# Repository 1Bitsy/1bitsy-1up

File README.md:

This repository contains the board and code used on the 1Bitsy 1UP.

## Intro

1Bitsy 1UP is a retro inspired handheld game console, the design is based
around the following __semi arbitrary constraints and requirements.__

* Formfactor: PCB the size of the inside of a GB DMG (the gray one) This will
  hopefully eventually allow us to put the 1UP pcb inside a modified GB DMG
  case, either original or new molds sold by several online stores.
* Main CPU: All code should be able to execute on a 1Bitsy that is fitted with
  an STM32F415RGT6. That particular chip (due to the package size) does not
  contain external ram support or LCD display engine. Making LCD drive little
  bit more tricky. It is a nice constraint that makes coding for the platform
  bit more of a challenge in the style of classic conloles and 8bit computers
  because it does not have enough memory for a full framebuffer. ("racing the
  beam" FTW)
* Main CPU Mounting: The board contains the 1Bitsy compatible low profile
  socket using [SL-115-TT-19](https://www.samtec.com/products/sl-115-tt-19)
  and [BBL-115-T-E](https://www.samtec.com/products/bbl-115-t-e) Samtec
  connectors as well as one MillMax PogoPin spring loaded SMD connector.
* LCD: The LCD is a 240x320 TFT display with capacitive touch, connected
  through the 8bit parallel interface to the 1Bitsy. This allows us to push the
  data speed to the display quite high and reach good framerates that would not
  be possible through the SPI interface. The capacitive touch screen adds an
  interesting aspect of control that was not available on classic consoles
  prior to DS. (That was also resistive not capacitive)
* Audio: We are connecting the STM32F4 built in DAC lines for audio generation.
  This is not as slick and good as an i2s part but will likely make things
  "interesting".
* Controls: The gamepad consists of the classic D-Pad, ABXY, Select, Start set
  of buttons. Because we have the capacitive touch no other analog controls are
  considered necessary.
* Storage: To simplify storing games and data in large quantities we have
  connected a microSD card over the SDIO interface to the STM32, allowing for
  reasonabely fast load and save times and maybe even some other interesting
  hacks.
* Expansion: The platform will receive future expansions and improvements that
  will strive to remain transparent. Meaning all code written for the first
  version of the platform should work either out of the box or only with very
  minor modifications.

The display used is a TFT LCD with I2C CapTouch and ILI9341 driver.

__The most basic design consists of:__
* 1Bitsy STM32F415RGT6 (168MHz, 192kb RAM, 1MB Flash)
* 240x320 2.8" TFT with capacitive touch and PWM backlight control
* D-Pad, ABXY, Start, Select buttons
* DAC audio out to headphones. (speakers optional)
* SDCard connected over SDIO interface

Second tier addons for quality of life:
* Lipo battery and charger built in
* Speaker audio

__Future "transparent" expansions:__
These expansions will contribute to new and interesting hacks possible on the
platform, they are not considered forward compatible but backward compatible.
This means that we do not anticipate the expansions to exist from the beginning
of the platform life and the software written at that time will not support the
future expansions, but the old software has to function as is or only with very
minor changes on the new device that contains the new expansions.

## Hacking

The board design is in the hardware subdirectory.

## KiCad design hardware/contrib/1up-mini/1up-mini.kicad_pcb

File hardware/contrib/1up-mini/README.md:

# 1up-mini

This is a board based on 1up v0.2, with horizontal form factor and easier to
solder by hand.

It is not supported by 1bit squared.

## What changed?

It aims to be fully compatible with 1up board. Some of the components are
changed to avoid hard to solder packages:

- Headphone amplifier reference is changed. It consumes more power than the
  one used on the original board.
- Volume control is the same component, with a different package.
- Battery charger and power path is split in two components.
- 0402 footprints are replaced with 0603.
- Touch screen signals are only connected to 6 pin connector.

Board shape is horizontal with symmetric buttons on both sides.

## What to change for the next iteration?

- 0603 and resistor network footprints are a little bit to small for hand
  soldering.
- SD card slot must be changed for something easier to solder.
- Headphone jack could be changed for something more solid.
- Hole for pogo pin is too small. Add a large pad so that it can be replaced
  with a cable.
- Switch are hard to source. Also the one I ordered are not so good.

## Assembly

Some tricky points:

- You will need solder paste, flux and hot air to solder the SD card slot.
- Surface under the LCD should be flat. Cut the pin used to mount the 1bitsy
  before soldering. Use isolating tape to avoid short circuits (there is a
  metal shield under the LCD).
- You can replace the pogo pin with a cable.

## BOM

| Reference              | Package    | Qty. | Designation     | Mouser/URL           |
| ---------------------- | ---------- | ---- | --------------- | -------------------- |
| C[19,26,27,29,30]      | 0603       | 5    | 100 nF          |                      |
| C[20,21,24,25,31..33]  | 0603       | 7    | 1 µF            |                      |
| C[22,23]               | 0603       | 2    | 2.2 µF          |                      |
| C28                    | 0805       | 1    | 10 µF           |                      |
| CON1                   | SCHA4B0419 | 1    | Micro SD        | 688-SCHA4B0419       |
| D2                     | 0603       | 1    | Yellow LED      |                      |
| J3                     | Jack       | 1    | JACK_3C1S       | 490-SJ2-35853BSMT-TR |
| P1                     | PogoPin    | 1    | PogoPin         | 575-906115 or cable  |
| P[2..4]                |            | 3    | Battery conn.   |                      |
| Q1                     | SOT-23     | 1    | NMOS            | 726-BSS806NH6327XT   |
| R11                    | 0603       | 1    | 49 kΩ           |                      |
| R[12..15]              | 4x0603     | 4    | 10 kΩ           | 667-EXB-38V103JV     |
| R[17,18]               | 0603       | 2    | 2.7 kΩ          |                      |
| R[20..23]              | 0603       | 4    | 10 Ω            |                      |
| R24                    | 0603       | 1    | 1 kΩ            |                      |
| R6                     | 0603       | 1    | 4.7 kΩ          |                      |
| R[7,10,16,19,25,26,30] | 0603       | 7    | 10 kΩ           |                      |
| R[8,9]                 | 0603       | 2    | 50 Ω            |                      |
| SW[12,13]              | Switch     | 2    | Side Switch     | 653-B3U-3000P        |
| SW14                   | Switch     | 1    | SPDT Switch     | 611-PCM12SMTR        |
| SW[2..11]              | Switch     | 1    | Switch          | [aliexpress][]       |
| U10                    | TSSOP-8    | 1    | TPS2111A        | 595-TPS2111APWR      |
| U2                     | 1bitsy     | 1    | 1bitsy          |                      |
| U3                     | TSSOP-14   | 1    | MCP4661-103E/ST | 579-MCP4661-103E/ST  |
| U4                     | TSSOP-14   | 1    | TPA6139A2-PW    | 595-TPA6139A2PWR     |
| U[5,6]                 | TSSOP-16   | 2    | 74HC165         | 771-74HC165PW-T      |
| U7                     | SOT-23-6   | 1    | BQ21040         | 595-BQ21040DBVR      |
| U8                     | ER-CON50HT | 1    | 50 pin conn.    | sold with LCD        |
| U9                     | ER-CON06HB | 1    | 6 pin conn.     | sold with LCD        |
| LCD                    |            | 1    | LCD             | [buydisplay][]       |

[buydisplay]:
  http://www.buydisplay.com/default/serial-spi-2-8-tft-lcd-module-display-320x240-optional-touch-screen
[aliexpress]:
  https://www.aliexpress.com/store/product/Original-new-100-Japan-conductive-rubber-head-waterproof-touch-switch-8-8-5-silent-key-micro/828867_32724415032.html

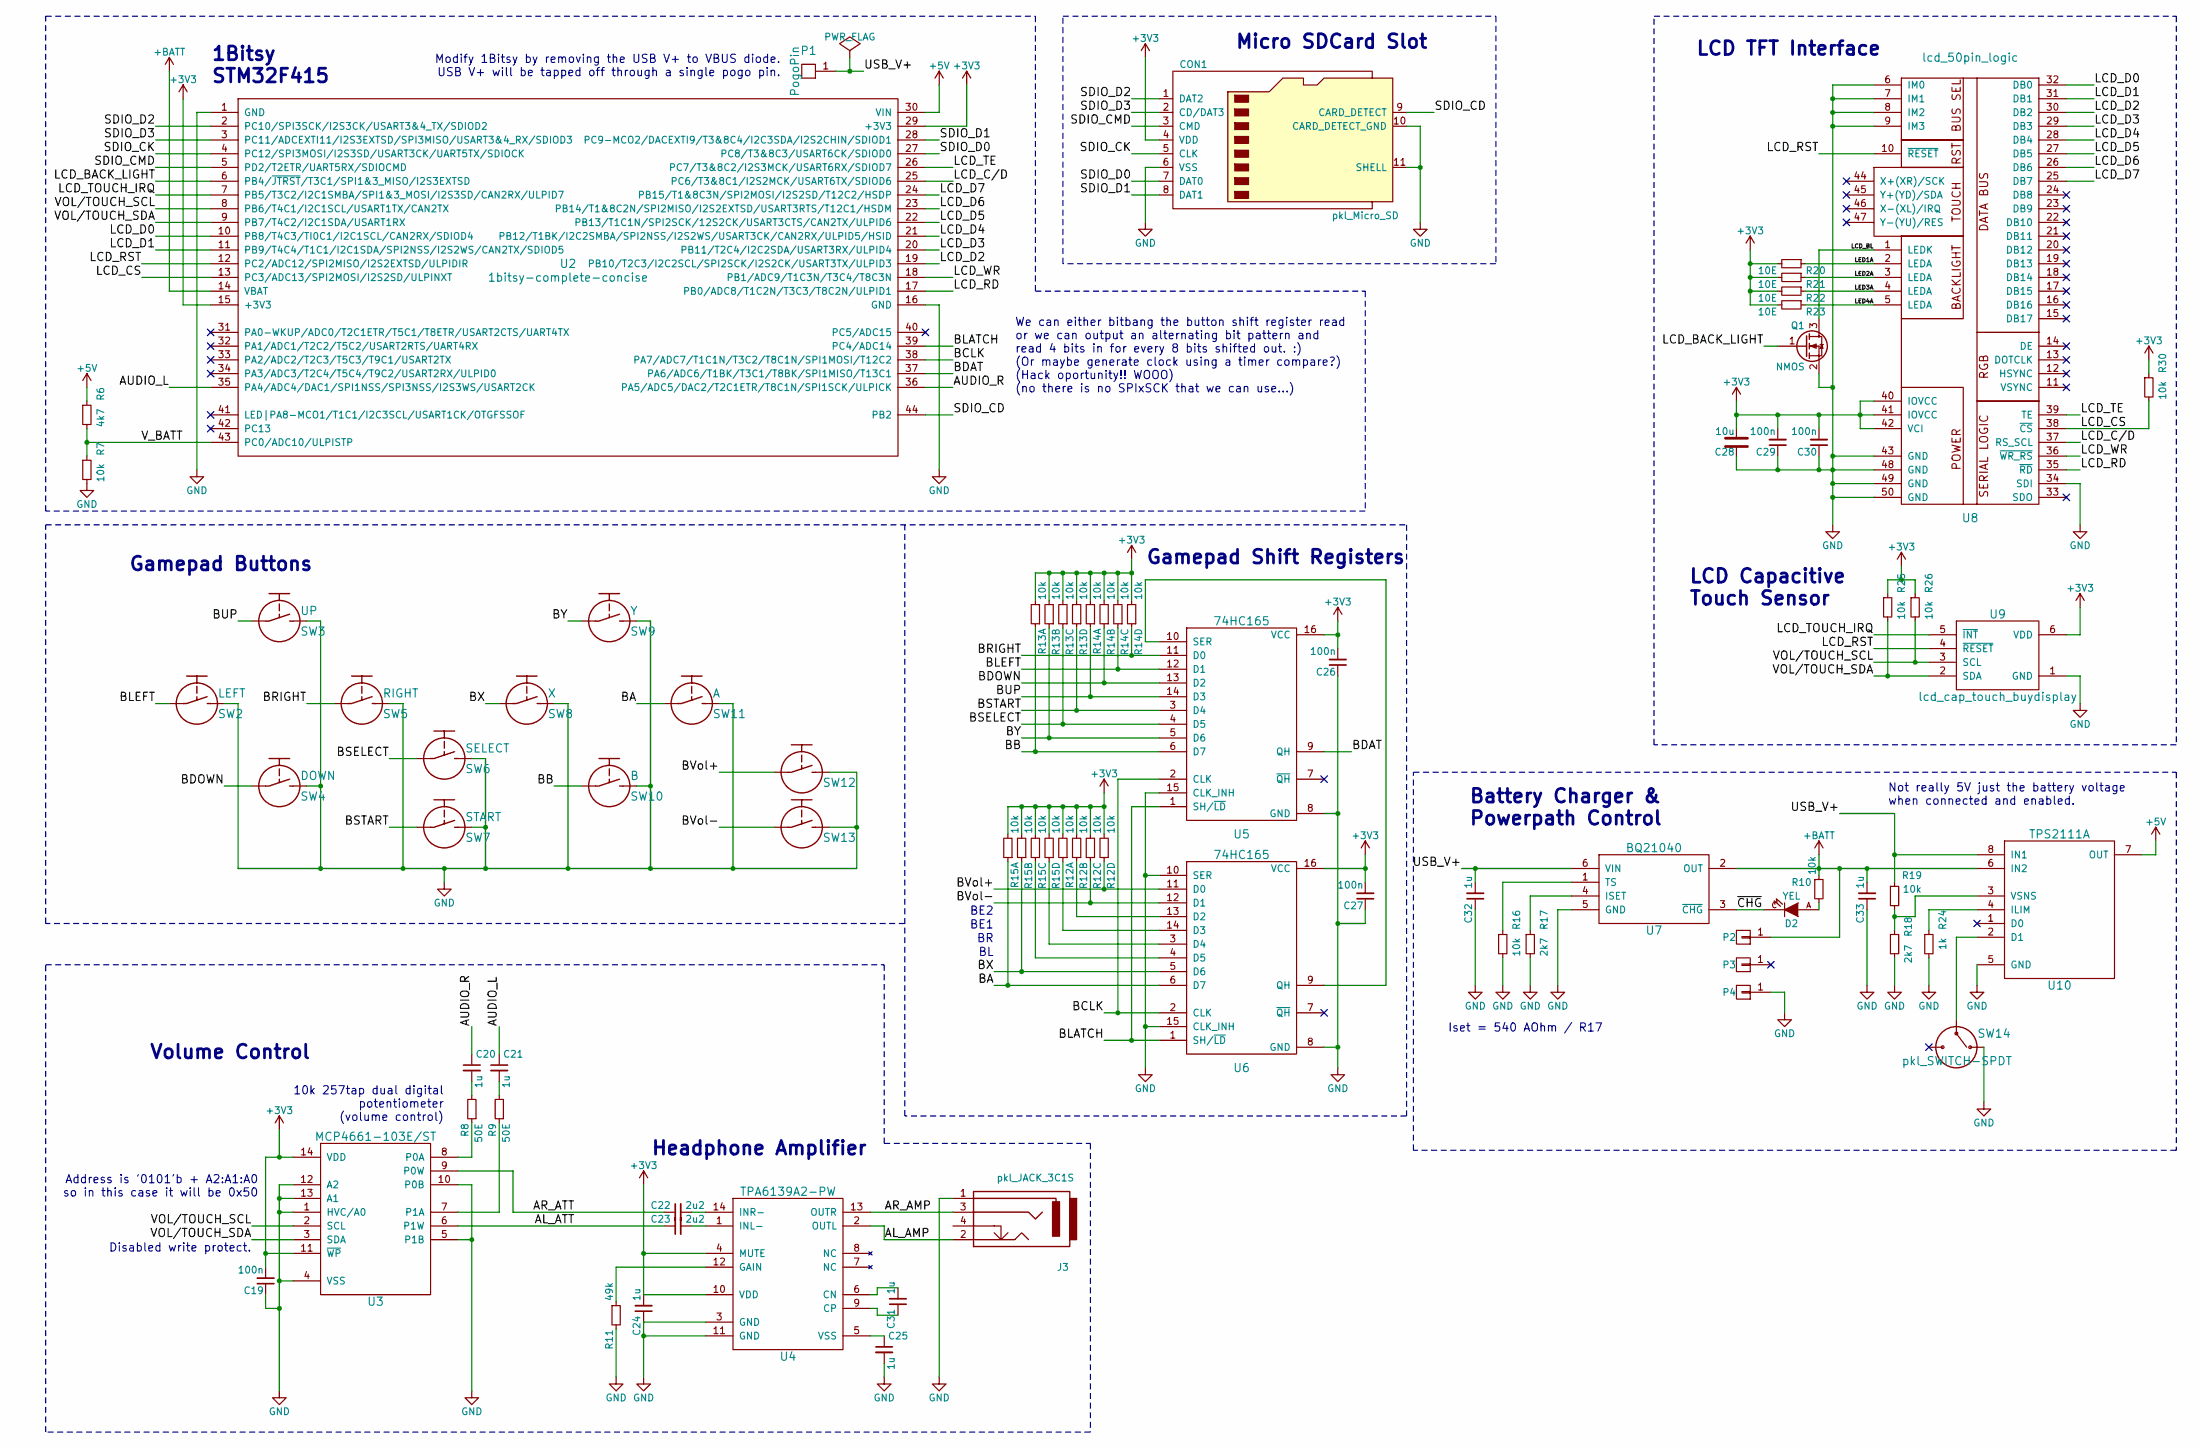
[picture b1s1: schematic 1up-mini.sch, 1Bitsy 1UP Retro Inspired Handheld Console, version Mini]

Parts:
C19, C26, C27, C29, C30: 100n; C_0603
C20, C21, C24, C25, C31, C32, C33: 1u; C_0603
C22, C23: 2u2; C_0603
C28: 10u; C_0805
CON1: pkl_Micro_SD; SCHA4B0419
D2: YEL; D_0603
J3: pkl_JACK_3C1S; SJ2-35853B-SMT
P1: PogoPin; PAD_MILL-MAX_0906
P2, P3, P4: CONN_01X01; Pin_Header_Straight_Round_1x01
Q1: NMOS; SOT-23
R6: 4k7; R_0603
R7, R10, R16, R19, R25, R26, R30: 10k; R_0603
R8, R9: 50E; R_0603
R11: 49k; R_0603
R12, R13, R14, R15: 10k; R_Array_Concave_4x0603
R17, R18: 2k7; R_0603
R20, R21, R22, R23: 10E; R_0603
R24: 1k; R_0603
SW2: LEFT; Tact_Switch_Top_TH_7.8MM_Snap
SW3: UP; Tact_Switch_Top_TH_7.8MM_Snap
SW4: DOWN; Tact_Switch_Top_TH_7.8MM_Snap
SW5: RIGHT; Tact_Switch_Top_TH_7.8MM_Snap
SW6: SELECT; Tact_Switch_Top_TH_7.8MM_Snap
SW7: START; Tact_Switch_Top_TH_7.8MM_Snap
SW8: X; Tact_Switch_Top_TH_7.8MM_Snap
SW9: Y; Tact_Switch_Top_TH_7.8MM_Snap
SW10: B; Tact_Switch_Top_TH_7.8MM_Snap
SW11: A; Tact_Switch_Top_TH_7.8MM_Snap
SW12, SW13: Tact_Switch_Side_B3U-3000P
SW14: pkl_SWITCH-SPDT; SW_SPDT_PCM12
U2: 1bitsy-complete-concise; 1bitsy-sl-1xx-xx-19
U3: MCP4661-103E/ST; TSSOP-14_4.4x5mm_Pitch0.65mm
U4: TPA6139A2-PW; TSSOP-14_4.4x5mm_Pitch0.65mm
U5, U6: 74HC165; TSSOP-16_4.4x5mm_Pitch0.65mm
U7: BQ21040; SOT-23-6
U8: lcd_50pin_logic; ER-CON50HT
U9: lcd_cap_touch_buydisplay; ER-CON06HB
U10: TPS2111A; TSSOP-8_4.4x3mm_Pitch0.65mm

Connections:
+3V3: C19.2, C24.2, C26.2, C27.2, C28.2, C29.2, C30.2, CON1.4 (VDD), R12.2, R12.4, R12.6, R12.8, R13.2, R13.4, R13.6, R13.8, R14.2, R14.4, R14.6, R14.8, R15.2, R15.4, R15.6, R15.8, R20.2, R21.2, R22.2, R23.2, R25.1, R26.1, R30.1, U2.15 (+3V3), U2.29 (+3V3), U3.11 (~WP), U3.14 (VDD), U4.4 (MUTE), U4.10 (VDD), U5.16 (VCC), U6.16 (VCC), U8.40 (IOVCC), U8.41 (IOVCC), U8.42 (VCI), U9.6 (VDD)
+5V: R6.1, U2.30 (VIN), U10.7 (OUT)
+BATT: C33.2, P2.1, R10.1, U2.14 (VBAT), U7.2 (OUT), U10.6 (IN2)
/AL_AMP: J3.2, U4.2 (OUTL)
/AL_ATT: C23.1, U3.6 (P1W)
/AR_AMP: J3.3, U4.13 (OUTR)
/AR_ATT: C22.1, U3.9 (P0W)
/AUDIO_L: C21.1, U2.35 (PA4/ADC4/DAC1/SPI1NSS/SPI3NSS/I2S3WS/US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)
/AUDIO_R: C20.1, U2.36 (PA5/ADC5/DAC2/T2C1ETR/T8C1N/SPI1SCK/ULP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)
/BA: R15.1, SW11.1, U6.6 (D7)
/BB: R13.1, SW10.1, U5.6 (D7)
/BCLK: U2.38 (PA7/ADC7/T1C1N/T3C2/T8C1N/SPI1MOSI/T12C2), U5.2 (CLK), U6.2 (CLK)
/BDAT: U2.37 (PA6/ADC6/T1BK/T3C1/T8BK/SPI1MISO/T13C1), U5.9 (QH)
/BDOWN: R14.3, SW4.1, U5.13 (D2)
/BLATCH: U2.39 (PC4/ADC14), U5.1 (SH/~LD), U6.1 (SH/~LD)
/BLEFT: R14.5, SW2.1, U5.12 (D1)
/BRIGHT: R14.7, SW5.1, U5.11 (D0)
/BSELECT: R13.5, SW6.1, U5.4 (D5)
/BSTART: R13.7, SW7.1, U5.3 (D4)
/BUP: R14.1, SW3.1, U5.14 (D3)
/BVol+: R12.7, SW12.1, U6.11 (D0)
/BVol-: R12.5, SW13.1, U6.12 (D1)
/BX: R15.3, SW8.1, U6.5 (D6)
/BY: R13.3, SW9.1, U5.5 (D6)
/LCD_BACK_LIGHT: Q1.1 (G), U2.6 (PB4/~JTRST~/T3C1/SPI1&3_MISO/I2S3EXTSD)
/LCD_BL: Q1.3 (D), U8.1 (LEDK)
/LCD_C/D: U2.25 (PC6/T3&8C1/I2S2MCK/USART6TX/SDIOD6), U8.37 (RS_SCL)
/LCD_CS: R30.2, U2.13 (PC3/ADC13/SPI2MOSI/I2S2SD/ULPINXT), U8.38 (~CS)
/LCD_D0: U2.10 (PB8/T4C3/TI0C1/I2C1SCL/CAN2RX/SDIOD4), U8.32 (DB0)
/LCD_D1: U2.11 (PB9/T4C4/T1C1/I2C1SDA/SPI2NSS/I2S2WS/CA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), U8.31 (DB1)
/LCD_D2: U2.19 (PB10/T2C3/I2C2SCL/SPI2SCK/I2S2CK/USART3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), U8.30 (DB2)
/LCD_D3: U2.20 (PB11/T2C4/I2C2SDA/USART3RX/ULPID4), U8.29 (DB3)
/LCD_D4: U2.21 (PB12/T1BK/I2C2SMBA/SPI2NSS/I2S2WS/USART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), U8.28 (DB4)
/LCD_D5: U2.22 (PB13/T1C1N/SPI2SCK/12S2CK/USART3CTS/CAN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), U8.27 (DB5)
/LCD_D6: U2.23 (PB14/T1&8C2N/SPI2MISO/I2S2EXTSD/USART3R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), U8.26 (DB6)
/LCD_D7: U2.24 (PB15/T1&8C3N/SPI2MOSI/I2S2SD/T12C2/HSDP), U8.25 (DB7)
/LCD_RD: U2.17 (PB0/ADC8/T1C2N/T3C3/T8C2N/ULPID1), U8.35 (~RD)
/LCD_RST: U2.12 (PC2/ADC12/SPI2MISO/I2S2EXTSD/ULPIDIR), U8.10 (~RESET), U9.4 (~RESET)
/LCD_TE: U2.26 (PC7/T3&8C2/I2S3MCK/USART6RX/SDIOD7), U8.39 (TE)
/LCD_TOUCH_IRQ: U2.7 (PB5/T3C2/I2C1SMBA/SPI1&3_MOSI/I2S3SD/CA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), U9.5 (~INT)
/LCD_WR: U2.18 (PB1/ADC9/T1C3N/T3C4/T8C3N), U8.36 (~WR_RS)
/LED1A: R20.1, U8.2 (LEDA)
/LED2A: R21.1, U8.3 (LEDA)
/LED3A: R22.1, U8.4 (LEDA)
/LED4A: R23.1, U8.5 (LEDA)
/SDIO_CD: CON1.9 (CARD_DETECT), U2.44 (PB2)
/SDIO_CK: CON1.5 (CLK), U2.4 (PC12/SPI3MOSI/I2S3SD/USART3CK/UART5TX/S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)
/SDIO_CMD: CON1.3 (CMD), U2.5 (PD2/T2ETR/UART5RX/SDIOCMD)
/SDIO_D0: CON1.7 (DAT0), U2.27 (PC8/T3&8C3/USART6CK/SDIOD0)
/SDIO_D1: CON1.8 (DAT1), U2.28 (PC9-MCO2/DACEXTI9/T3&8C4/I2C3SDA/I2S2CH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)
/SDIO_D2: CON1.1 (DAT2), U2.2 (PC10/SPI3SCK/I2S3CK/USART3&4_TX/SDIOD2)
/SDIO_D3: CON1.2 (CD/DAT3), U2.3 (PC11/ADCEXTI11/I2S3EXTSD/SPI3MISO/USART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)
/USB_V+: C32.2, P1.1, R19.1, U7.6 (VIN), U10.8 (IN1)
/VOL/TOUCH_SCL: R26.2, U2.8 (PB6/T4C1/I2C1SCL/USART1TX/CAN2TX), U3.2 (SCL), U9.3 (SCL)
/VOL/TOUCH_SDA: R25.2, U2.9 (PB7/T4C2/I2C1SDA/USART1RX), U3.3 (SDA), U9.2 (SDA)
/V_BATT: R6.2, R7.1, U2.43 (PC0/ADC10/ULPISTP)
/~CHG: D2.C, U7.3 (~CHG)
GND: C19.1, C24.1, C25.2, C26.1, C27.1, C28.1, C29.1, C30.1, C32.1, C33.1, CON1.6 (VSS), CON1.10 (CARD_DETECT_GND), CON1.11 (SHELL), J3.1, P4.1, Q1.2 (S), R7.2, R11.2, R16.2, R17.2, R18.2, R24.2, SW2.2, SW3.2, SW4.2, SW5.2, SW6.2, SW7.2, SW8.2, SW9.2, SW10.2, SW11.2, SW12.2, SW13.2, SW14.1, U2.1 (GND), U2.16 (GND), U3.1 (HVC/A0), U3.4 (VSS), U3.5 (P1B), U3.10 (P0B), U3.12 (A2), U3.13 (A1), U4.3 (GND), U4.11 (GND), U5.8 (GND), U5.15 (CLK_INH), U6.8 (GND), U6.10 (SER), U6.15 (CLK_INH), U7.5 (GND), U8.6 (IM0), U8.7 (IM1), U8.8 (IM2), U8.9 (IM3), U8.34 (SDI), U8.43 (GND), U8.48 (GND), U8.49 (GND), U8.50 (GND), U9.1 (GND), U10.5 (GND)
unnamed: C20.2, R8.2
unnamed: C21.2, R9.2
unnamed: C22.2, U4.14 (INR-)
unnamed: C23.2, U4.1 (INL-)
unnamed: C25.1, U4.5 (VSS)
unnamed: C31.1, U4.9 (CP)
unnamed: C31.2, U4.6 (CN)
unnamed: D2.A, R10.2
unnamed: R8.1, U3.8 (P0A)
unnamed: R9.1, U3.7 (P1A)
unnamed: R11.1, U4.12 (GAIN)
unnamed: R12.1, U6.14 (D3)
unnamed: R12.3, U6.13 (D2)
unnamed: R15.5, U6.4 (D5)
unnamed: R15.7, U6.3 (D4)
unnamed: R16.1, U7.1 (TS)
unnamed: R17.1, U7.4 (ISET)
unnamed: R18.1, R19.2, U10.3 (VSNS)
unnamed: R24.1, U10.4 (ILIM)
unnamed: SW14.2, U10.2 (D1)
unnamed: U5.10 (SER), U6.9 (QH)

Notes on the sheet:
BE1
BE2
Not really 5V just the battery voltage when connected and enabled.
Address is '0101'b + A2:A1:A0 so in this case it will be 0x50
Disabled write protect.
10k 257tap dual digital potentiometer (volume control)
LCD TFT Interface
LCD Capacitive Touch Sensor
Gamepad Buttons
Gamepad Shift Registers
Battery Charger & Powerpath Control
Volume Control
Headphone Amplifier
Iset = 540 AOhm / R17
Modify 1Bitsy by removing the USB V+ to VBUS diode. USB V+ will be tapped off through a single pogo pin.
We can either bitbang the button shift register read or we can output an alternating bit pattern and read 4 bits in for every 8 bits shifted out. :) (Or maybe generate clock using a timer compare?) (Hack oportunity!! WOOO) (no there is no SPIxSCK that we can use...)
Micro SDCard Slot
1Bitsy STM32F415

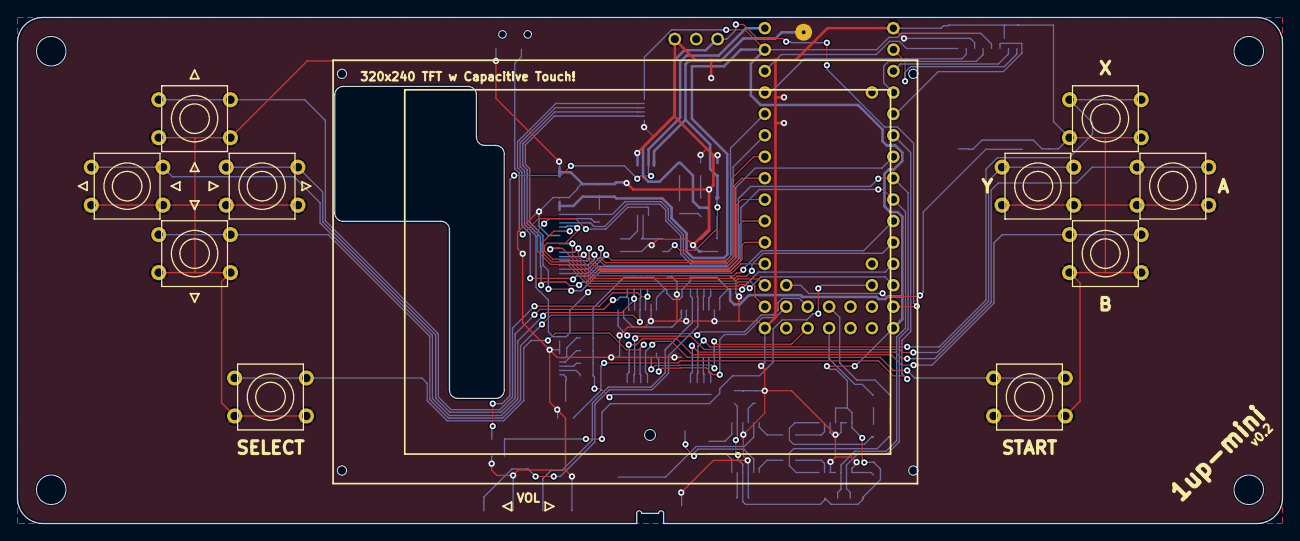
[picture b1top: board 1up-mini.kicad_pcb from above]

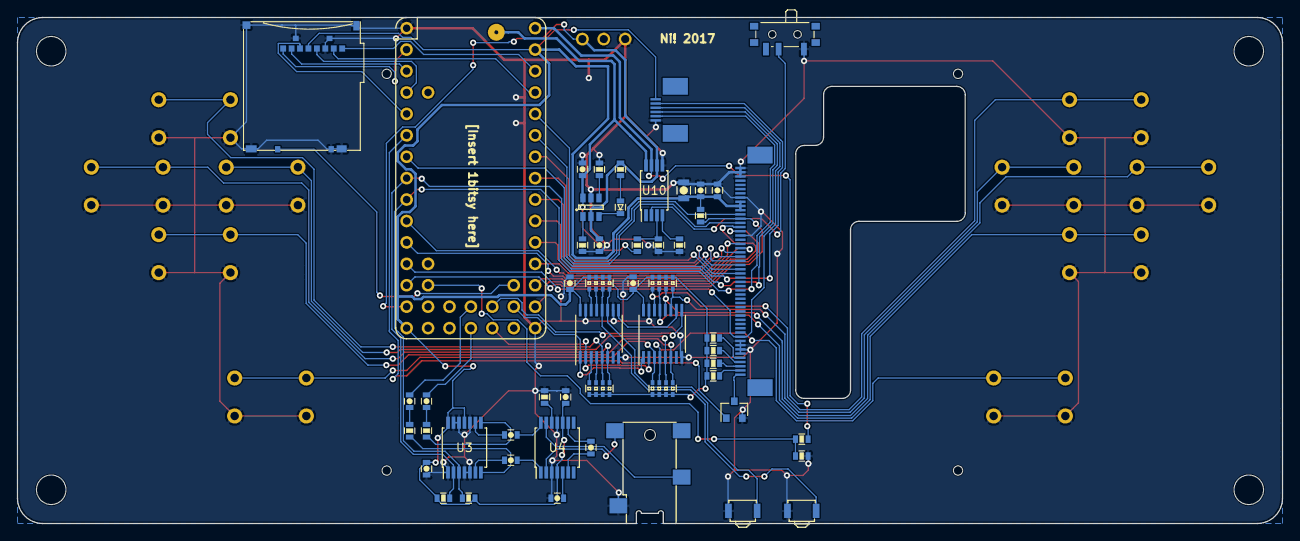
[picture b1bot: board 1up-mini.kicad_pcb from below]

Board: 2 copper layers, 150.0 x 60.0 mm, 67 parts (57 on the bottom side), 79 nets.

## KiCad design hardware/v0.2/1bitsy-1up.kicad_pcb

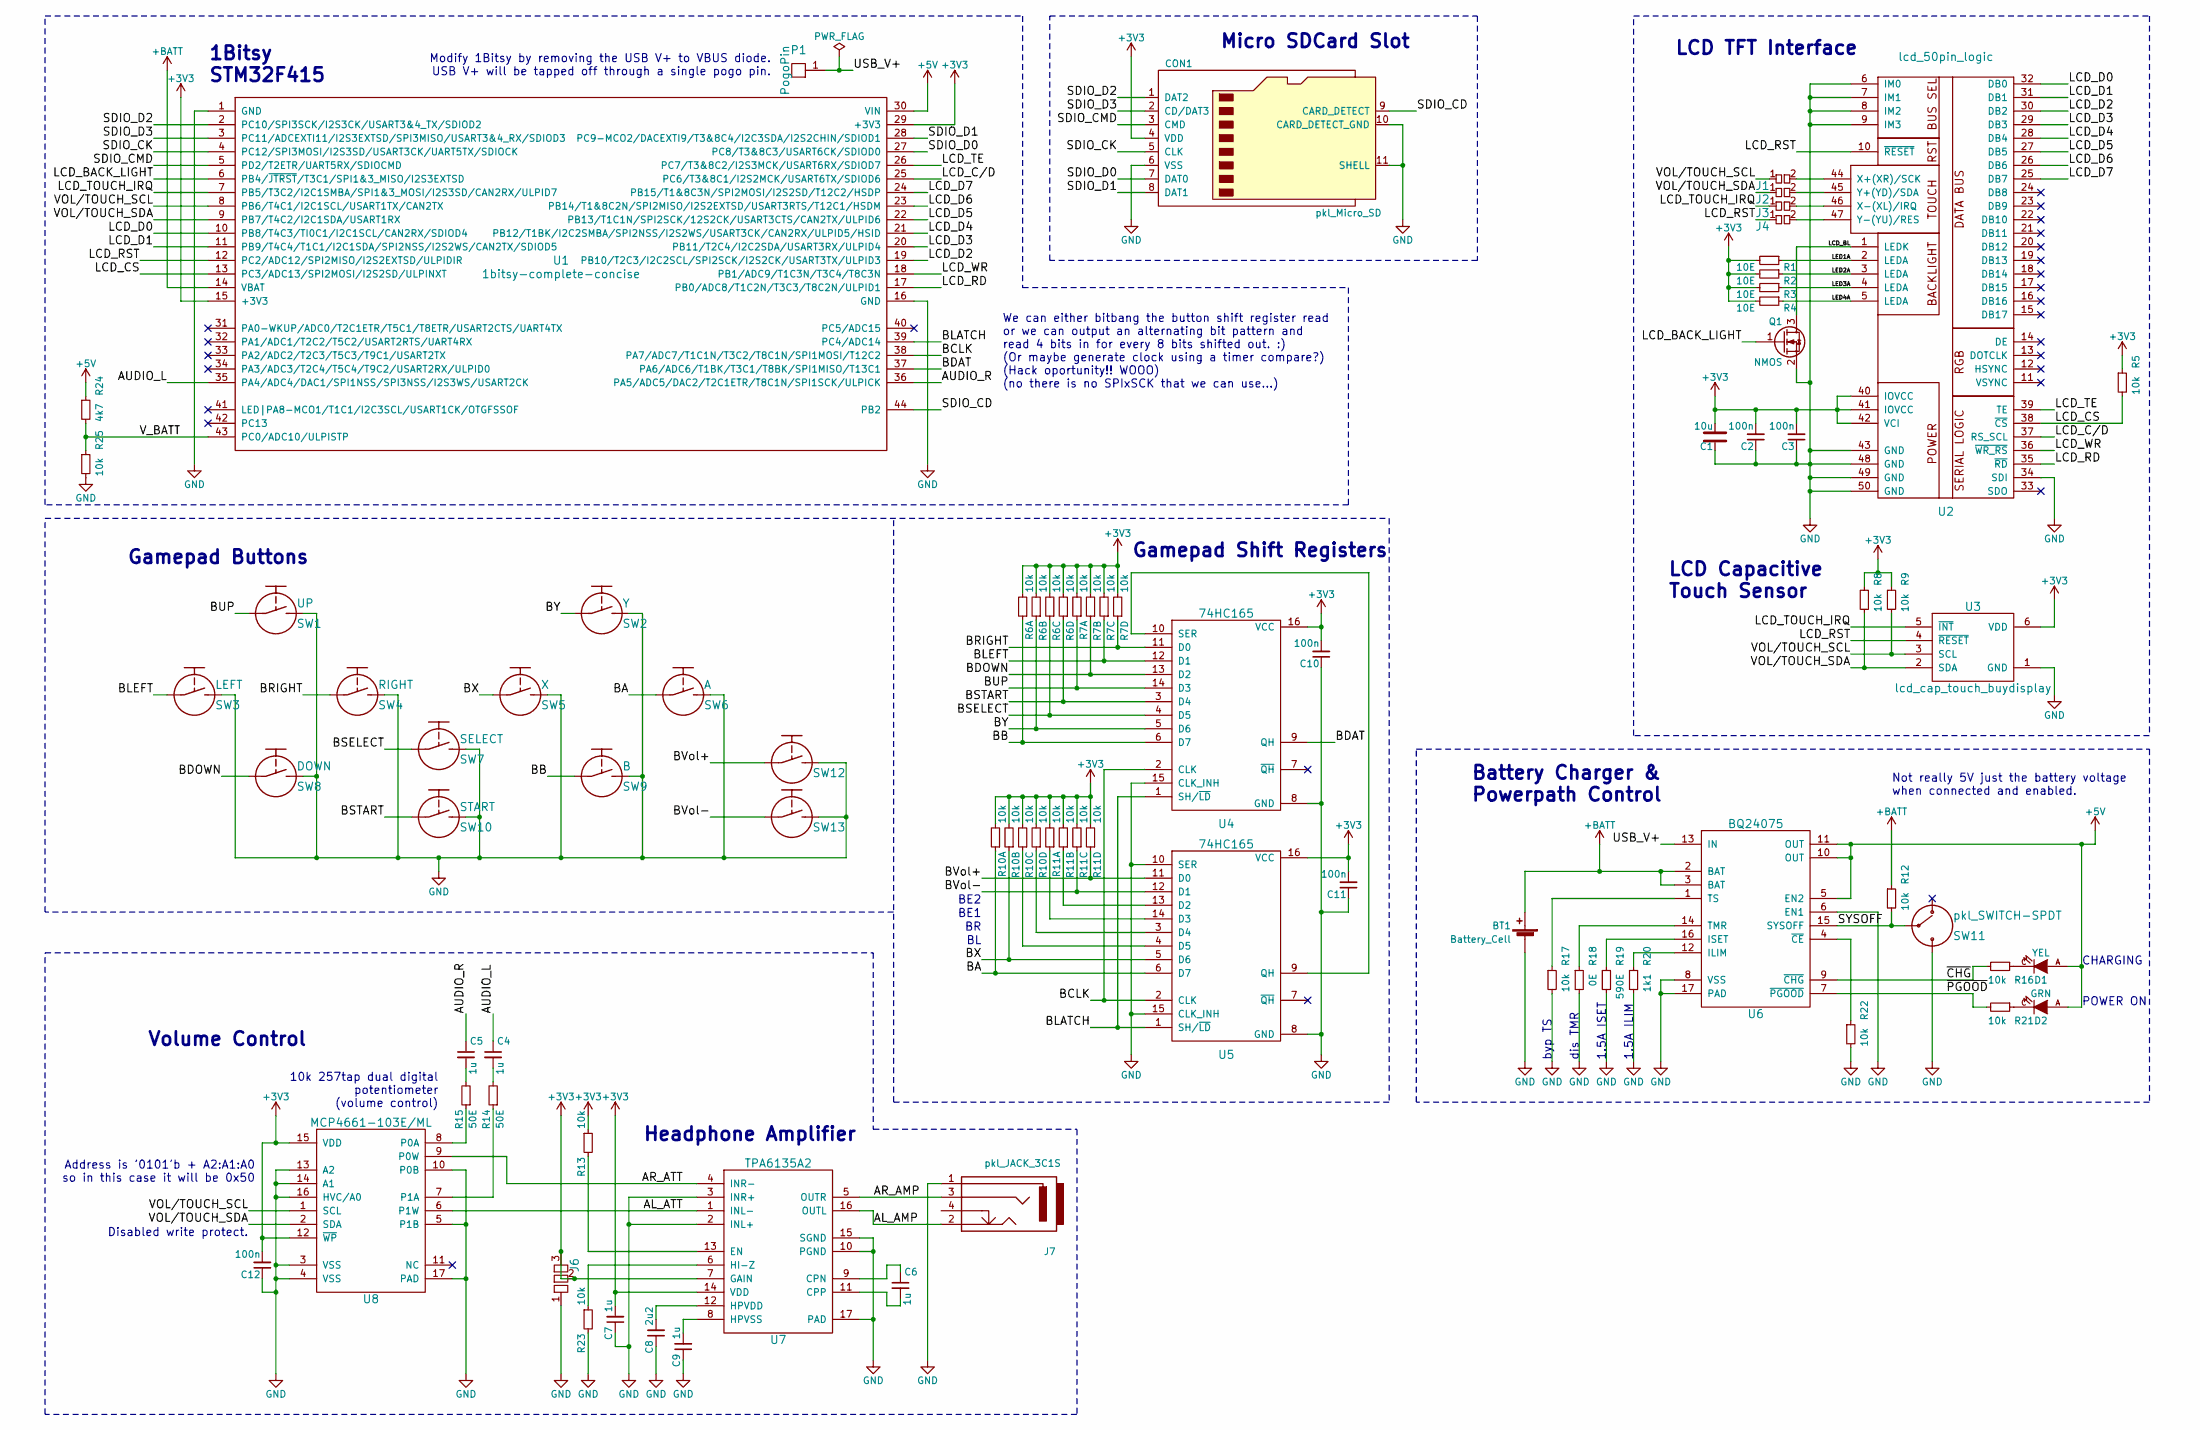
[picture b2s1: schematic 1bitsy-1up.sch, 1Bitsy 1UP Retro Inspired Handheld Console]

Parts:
BT1: Battery_Cell; BATTERY_CLIP_18650
C1: 10u; C_0805
C2, C3, C10, C11, C12: 100n; C_0402
C4, C5, C6, C7, C9: 1u; C_0402
C8: 2u2; C_0402
CON1: pkl_Micro_SD; SCHA4B0419
D1: YEL; D_0603
D2: GRN; D_0603
J1, J2, J3, J4: pkl_jumper; J_0402
J6: Jumper_Dual; J_0602
J7: pkl_JACK_3C1S; SJ2-35853B-SMT
P1: PogoPin; PAD_MILL-MAX_0906
Q1: NMOS; SOT-23
R1, R2, R3, R4: 10E; R_0603
R5, R8, R9, R12, R13, R16, R17, R21, R22, R23, R25: 10k; R_0402
R6, R7, R10, R11: 10k; R_Array_Convex_4x0402
R14, R15: 50E; R_0402
R18: 0E; R_0402
R19: 590E; R_0402
R20: 1k1; R_0402
R24: 4k7; R_0402
SW1: UP; Tact_Switch_Top_TH_7.8MM_Snap
SW2: Y; Tact_Switch_Top_TH_7.8MM_Snap
SW3: LEFT; Tact_Switch_Top_TH_7.8MM_Snap
SW4: RIGHT; Tact_Switch_Top_TH_7.8MM_Snap
SW5: X; Tact_Switch_Top_TH_7.8MM_Snap
SW6: A; Tact_Switch_Top_TH_7.8MM_Snap
SW7: SELECT; Tact_Switch_Top_TH_7.8MM_Snap
SW8: DOWN; Tact_Switch_Top_TH_7.8MM_Snap
SW9: B; Tact_Switch_Top_TH_7.8MM_Snap
SW10: START; Tact_Switch_Top_TH_7.8MM_Snap
SW11: pkl_SWITCH-SPDT; SW_SPDT_PCM12
SW12, SW13: Tact_Switch_Side_B3U-3000P
U1: 1bitsy-complete-concise; 1bitsy-sl-1xx-xx-19
U2: lcd_50pin_logic; ER-CON50HT
U3: lcd_cap_touch_buydisplay; ER-CON06HB
U4, U5: 74HC165; TSSOP-16_4.4x5mm_Pitch0.65mm
U6: BQ24075; QFN-16-1EP_3x3mm_Pitch0.5mm
U7: TPA6135A2; QFN-16-1EP_3x3mm_Pitch0.5mm
U8: MCP4661-103E/ML; QFN-16-1EP_4x4mm_Pitch0.65mm

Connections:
+3V3: C1.2, C2.2, C3.2, C7.2, C10.2, C11.2, C12.2, CON1.4 (VDD), J6.2, J6.3, R1.2, R2.2, R3.2, R4.2, R5.1, R6.2, R6.4, R6.6, R6.8, R7.2, R7.4, R7.6, R7.8, R8.1, R9.1, R10.2, R10.4, R10.6, R10.8, R11.2, R11.4, R11.6, R11.8, R13.1, U1.15 (+3V3), U1.29 (+3V3), U2.40 (IOVCC), U2.41 (IOVCC), U2.42 (VCI), U3.6 (VDD), U4.16 (VCC), U5.16 (VCC), U7.7 (GAIN), U7.14 (VDD), U8.12 (~WP), U8.15 (VDD)
+5V: D1.A, D2.A, R24.1, U1.30 (VIN), U6.5 (EN2), U6.10 (OUT), U6.11 (OUT)
+BATT: BT1.1 (+), R12.1, U1.14 (VBAT), U6.2 (BAT), U6.3 (BAT)
/AL_AMP: J7.2, U7.16 (OUTL)
/AL_ATT: U7.1 (INL-), U8.6 (P1W)
/AR_AMP: J7.3, U7.5 (OUTR)
/AR_ATT: U7.4 (INR-), U8.9 (P0W)
/AUDIO_L: C4.1, U1.35 (PA4/ADC4/DAC1/SPI1NSS/SPI3NSS/I2S3WS/US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)
/AUDIO_R: C5.1, U1.36 (PA5/ADC5/DAC2/T2C1ETR/T8C1N/SPI1SCK/ULP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)
/BA: R10.1, SW6.1, U5.6 (D7)
/BB: R6.1, SW9.1, U4.6 (D7)
/BCLK: U1.38 (PA7/ADC7/T1C1N/T3C2/T8C1N/SPI1MOSI/T12C2), U4.2 (CLK), U5.2 (CLK)
/BDAT: U1.37 (PA6/ADC6/T1BK/T3C1/T8BK/SPI1MISO/T13C1), U4.9 (QH)
/BDOWN: R7.3, SW8.1, U4.13 (D2)
/BLATCH: U1.39 (PC4/ADC14), U4.1 (SH/~LD), U5.1 (SH/~LD)
/BLEFT: R7.5, SW3.1, U4.12 (D1)
/BRIGHT: R7.7, SW4.1, U4.11 (D0)
/BSELECT: R6.5, SW7.1, U4.4 (D5)
/BSTART: R6.7, SW10.1, U4.3 (D4)
/BUP: R7.1, SW1.1, U4.14 (D3)
/BVol+: R11.7, SW12.1, U5.11 (D0)
/BVol-: R11.5, SW13.1, U5.12 (D1)
/BX: R10.3, SW5.1, U5.5 (D6)
/BY: R6.3, SW2.1, U4.5 (D6)
/LCD_BACK_LIGHT: Q1.1 (G), U1.6 (PB4/~JTRST~/T3C1/SPI1&3_MISO/I2S3EXTSD)
/LCD_BL: Q1.3 (D), U2.1 (LEDK)
/LCD_C/D: U1.25 (PC6/T3&8C1/I2S2MCK/USART6TX/SDIOD6), U2.37 (RS_SCL)
/LCD_CS: R5.2, U1.13 (PC3/ADC13/SPI2MOSI/I2S2SD/ULPINXT), U2.38 (~CS)
/LCD_D0: U1.10 (PB8/T4C3/TI0C1/I2C1SCL/CAN2RX/SDIOD4), U2.32 (DB0)
/LCD_D1: U1.11 (PB9/T4C4/T1C1/I2C1SDA/SPI2NSS/I2S2WS/CA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), U2.31 (DB1)
/LCD_D2: U1.19 (PB10/T2C3/I2C2SCL/SPI2SCK/I2S2CK/USART3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), U2.30 (DB2)
/LCD_D3: U1.20 (PB11/T2C4/I2C2SDA/USART3RX/ULPID4), U2.29 (DB3)
/LCD_D4: U1.21 (PB12/T1BK/I2C2SMBA/SPI2NSS/I2S2WS/USART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), U2.28 (DB4)
/LCD_D5: U1.22 (PB13/T1C1N/SPI2SCK/12S2CK/USART3CTS/CAN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), U2.27 (DB5)
/LCD_D6: U1.23 (PB14/T1&8C2N/SPI2MISO/I2S2EXTSD/USART3R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), U2.26 (DB6)
/LCD_D7: U1.24 (PB15/T1&8C3N/SPI2MOSI/I2S2SD/T12C2/HSDP), U2.25 (DB7)
/LCD_RD: U1.17 (PB0/ADC8/T1C2N/T3C3/T8C2N/ULPID1), U2.35 (~RD)
/LCD_RST: J4.1, U1.12 (PC2/ADC12/SPI2MISO/I2S2EXTSD/ULPIDIR), U2.10 (~RESET), U3.4 (~RESET)
/LCD_TE: U1.26 (PC7/T3&8C2/I2S3MCK/USART6RX/SDIOD7), U2.39 (TE)
/LCD_TOUCH_IRQ: J3.1, U1.7 (PB5/T3C2/I2C1SMBA/SPI1&3_MOSI/I2S3SD/CA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), U3.5 (~INT)
/LCD_WR: U1.18 (PB1/ADC9/T1C3N/T3C4/T8C3N), U2.36 (~WR_RS)
/LED1A: R1.1, U2.2 (LEDA)
/LED2A: R2.1, U2.3 (LEDA)
/LED3A: R3.1, U2.4 (LEDA)
/LED4A: R4.1, U2.5 (LEDA)
/SDIO_CD: CON1.9 (CARD_DETECT), U1.44 (PB2)
/SDIO_CK: CON1.5 (CLK), U1.4 (PC12/SPI3MOSI/I2S3SD/USART3CK/UART5TX/S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)
/SDIO_CMD: CON1.3 (CMD), U1.5 (PD2/T2ETR/UART5RX/SDIOCMD)
/SDIO_D0: CON1.7 (DAT0), U1.27 (PC8/T3&8C3/USART6CK/SDIOD0)
/SDIO_D1: CON1.8 (DAT1), U1.28 (PC9-MCO2/DACEXTI9/T3&8C4/I2C3SDA/I2S2CH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)
/SDIO_D2: CON1.1 (DAT2), U1.2 (PC10/SPI3SCK/I2S3CK/USART3&4_TX/SDIOD2)
/SDIO_D3: CON1.2 (CD/DAT3), U1.3 (PC11/ADCEXTI11/I2S3EXTSD/SPI3MISO/USART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)
/SYSOFF: R12.2, SW11.2, U6.15 (SYSOFF)
/USB_V+: P1.1, U6.13 (IN)
/VOL/TOUCH_SCL: J1.1, R9.2, U1.8 (PB6/T4C1/I2C1SCL/USART1TX/CAN2TX), U3.3 (SCL), U8.1 (SCL)
/VOL/TOUCH_SDA: J2.1, R8.2, U1.9 (PB7/T4C2/I2C1SDA/USART1RX), U3.2 (SDA), U8.2 (SDA)
/V_BATT: R24.2, R25.1, U1.43 (PC0/ADC10/ULPISTP)
/~CHG: R16.2, U6.9 (~CHG)
/~PGOOD: R21.2, U6.7 (~PGOOD)
GND: BT1.2 (-), C1.1, C2.1, C3.1, C7.1, C8.1, C9.1, C10.1, C11.1, C12.1, CON1.6 (VSS), CON1.10 (CARD_DETECT_GND), CON1.11 (SHELL), J6.1, J7.1, Q1.2 (S), R17.2, R18.2, R19.2, R20.2, R22.2, R23.2, R25.2, SW1.2, SW2.2, SW3.2, SW4.2, SW5.2, SW6.2, SW7.2, SW8.2, SW9.2, SW10.2, SW11.3, SW12.2, SW13.2, U1.1 (GND), U1.16 (GND), U2.6 (IM0), U2.7 (IM1), U2.8 (IM2), U2.9 (IM3), U2.34 (SDI), U2.43 (GND), U2.48 (GND), U2.49 (GND), U2.50 (GND), U3.1 (GND), U4.8 (GND), U4.15 (CLK_INH), U5.8 (GND), U5.10 (SER), U5.15 (CLK_INH), U6.6 (EN1), U6.8 (VSS), U6.17 (PAD), U7.2 (INL+), U7.3 (INR+), U7.10 (PGND), U7.15 (SGND), U7.17 (PAD), U8.3 (VSS), U8.4 (VSS), U8.5 (P1B), U8.10 (P0B), U8.13 (A2), U8.14 (A1), U8.16 (HVC/A0), U8.17 (PAD)
unnamed: C4.2, R14.2
unnamed: C5.2, R15.2
unnamed: C6.1, U7.9 (CPN)
unnamed: C6.2, U7.11 (CPP)
unnamed: C8.2, U7.12 (HPVDD)
unnamed: C9.2, U7.8 (HPVSS)
unnamed: D1.C, R16.1
unnamed: D2.C, R21.1
unnamed: J1.2, U2.44 (X+(XR)/SCK)
unnamed: J2.2, U2.45 (Y+(YD)/SDA)
unnamed: J3.2, U2.46 (X-(XL)/IRQ)
unnamed: J4.2, U2.47 (Y-(YU)/RES)
unnamed: R10.5, U5.4 (D5)
unnamed: R10.7, U5.3 (D4)
unnamed: R11.1, U5.14 (D3)
unnamed: R11.3, U5.13 (D2)
unnamed: R13.2, U7.13 (EN)
unnamed: R14.1, U8.7 (P1A)
unnamed: R15.1, U8.8 (P0A)
unnamed: R17.1, U6.1 (TS)
unnamed: R18.1, U6.14 (TMR)
unnamed: R19.1, U6.16 (ISET)
unnamed: R20.1, U6.12 (ILIM)
unnamed: R22.1, U6.4 (~CE)
unnamed: R23.1, U7.6 (HI-Z)
unnamed: U4.10 (SER), U5.9 (QH)

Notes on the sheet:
1.5A ILIM
1.5A ISET
dis TMR
byp TS
POWER ON
CHARGING
Modify 1Bitsy by removing the USB V+ to VBUS diode. USB V+ will be tapped off through a single pogo pin.
We can either bitbang the button shift register read or we can output an alternating bit pattern and read 4 bits in for every 8 bits shifted out. :) (Or maybe generate clock using a timer compare?) (Hack oportunity!! WOOO) (no there is no SPIxSCK that we can use...)
BE1
BE2
Not really 5V just the battery voltage when connected and enabled.
Address is '0101'b + A2:A1:A0 so in this case it will be 0x50
Disabled write protect.
10k 257tap dual digital potentiometer (volume control)
Micro SDCard Slot
LCD TFT Interface
LCD Capacitive Touch Sensor
1Bitsy STM32F415
Gamepad Buttons
Gamepad Shift Registers
Battery Charger & Powerpath Control
Volume Control
Headphone Amplifier

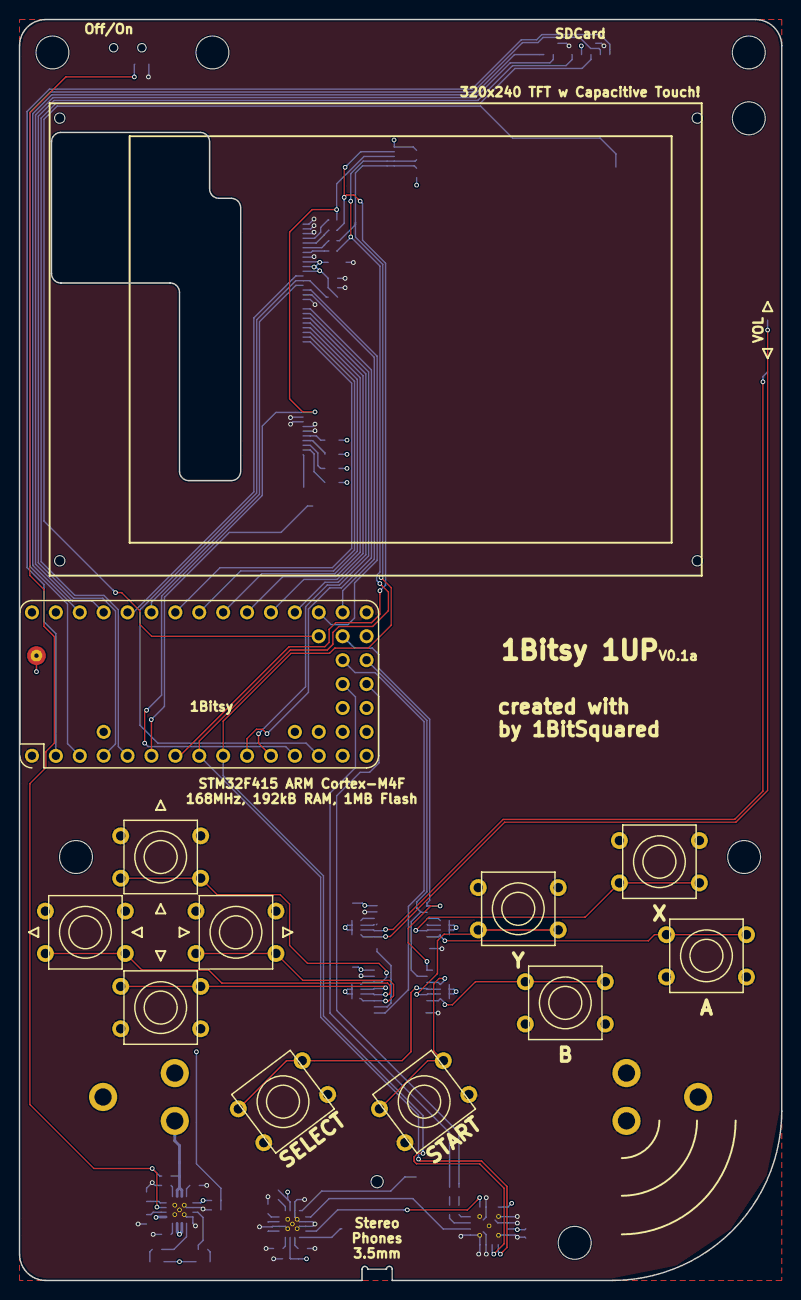
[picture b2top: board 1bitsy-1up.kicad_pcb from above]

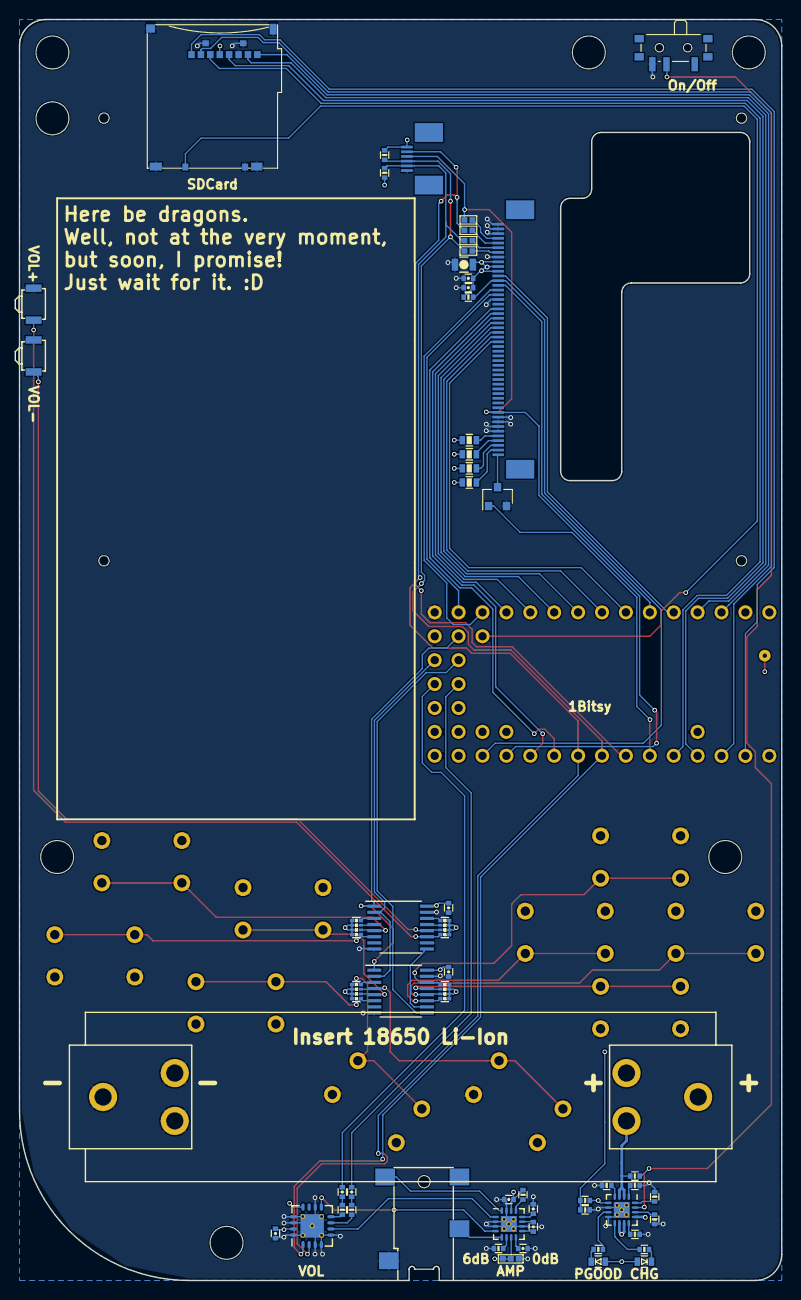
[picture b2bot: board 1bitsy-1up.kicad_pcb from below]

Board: 4 copper layers, 81.0 x 134.0 mm, 70 parts (58 on the bottom side), 86 nets.

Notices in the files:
hardware/V0.1/1bitsy-1up.sch:
(C) 2017 Piotr Esden-Tempski
(C) 2017 1BitSquared LLC
License: CC-BY-SA 4.0
hardware/contrib/1up-mini/1up-mini.kicad_pcb:
License: CC-BY-SA V4.0
hardware/contrib/1up-mini/1up-mini.sch:
(C) 2017 Nicolas Schodet
